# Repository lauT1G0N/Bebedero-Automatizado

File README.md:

el proyecto se trata de un bebedero automatizado para animales atreves de WI-FI
        tiene la capacidad de medir el nivel del agua y autoabastecer la misma ,

ES UN PROYECTO ENFOCADO EN LA PREVENCION DEL DESPERDICIO DE AGUA Y EN LA AUTOMATIZACION PARA AGILIZAR EL TIMEPO

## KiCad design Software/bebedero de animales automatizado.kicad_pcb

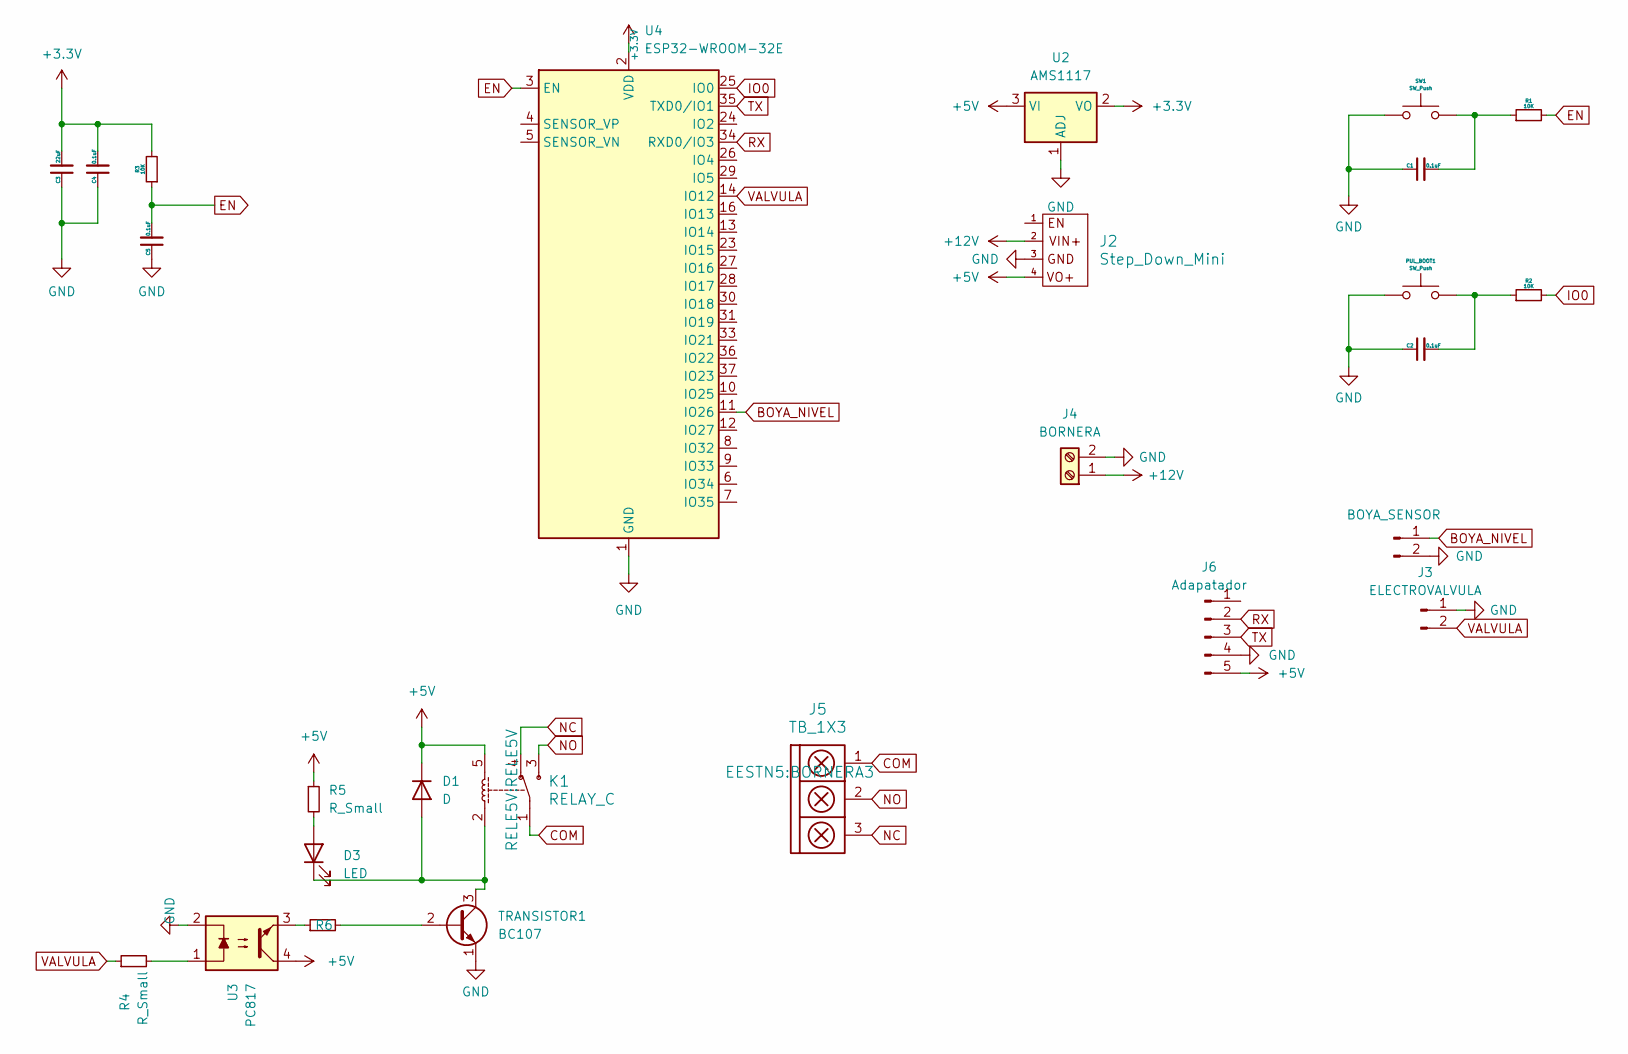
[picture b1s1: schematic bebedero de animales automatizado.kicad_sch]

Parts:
C1, C2, C4, C5: 0.1uF; C_0805
C3: 22uF; C_0805
D1: D; D_0805_2012Metric
D3: LED; LED_0805_2012Metric
J1: BOYA_SENSOR; PinHeader_1x02_P2.54mm_Vertical
J2: Step_Down_Mini; Mini360
J3: ELECTROVALVULA; PinHeader_1x02_P2.54mm_Vertical
J4: BORNERA; BORNERA2_AZUL
J5: TB_1X3; BORNERA3
J6: Adapatador; PinHeader_1x05_P2.54mm_Vertical
K1: RELAY_C; RELE5V
PUL_BOOT1: SW_Push; SW_PUSH_6mm_H5mm
R1, R2, R3: 10K; R_0805_2012Metric
R4, R5, R6: R_Small; R_0805_2012Metric
SW1: SW_Push; SW_PUSH_6mm_H5mm
TRANSISTOR1: BC107; TO-18-3
U2: AMS1117; SOT223-TAB2
U3: PC817; SOIC254P960X420-4N
U4: ESP32-WROOM-32E; ESP32-WROOM-32D

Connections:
+3.3V: C3.2, C4.2, R3.2, U2.2 (VO), U4.2 (VDD)
+5V: D1.1 (K), J2.4, J6.5, K1.5, R5.1, U2.3 (VI), U3.4
+12V: J2.2, J4.1
BOYA_NIVEL: J1.1, U4.11 (IO26)
COM: J5.1, K1.1
EN: C5.2, R1.2, R3.1, U4.3 (EN)
GND: C1.1, C2.1, C3.1, C4.1, C5.1, J1.2, J2.3, J3.1, J4.2, J6.4, PUL_BOOT1.1, SW1.1, TRANSISTOR1.1 (E), U2.1 (ADJ), U3.2, U4.1 (GND), U4.15 (GND), U4.38 (GND), U4.39 (GND)
IO0: R2.2, U4.25 (IO0)
NC: J5.3, K1.4
NO: J5.2, K1.3
unnamed: C1.2, R1.1, SW1.2
unnamed: C2.2, PUL_BOOT1.2, R2.1
unnamed: D1.2 (A), D3.1 (K), K1.2, TRANSISTOR1.3 (C)
unnamed: D3.2 (A), R5.2
unnamed: R4.2, U3.1
unnamed: R6.1, U3.3
unnamed: R6.2, TRANSISTOR1.2 (B)
RX: J6.2, U4.34 (RXD0/IO3)
TX: J6.3, U4.35 (TXD0/IO1)
VALVULA: J3.2, R4.1, U4.14 (IO12)

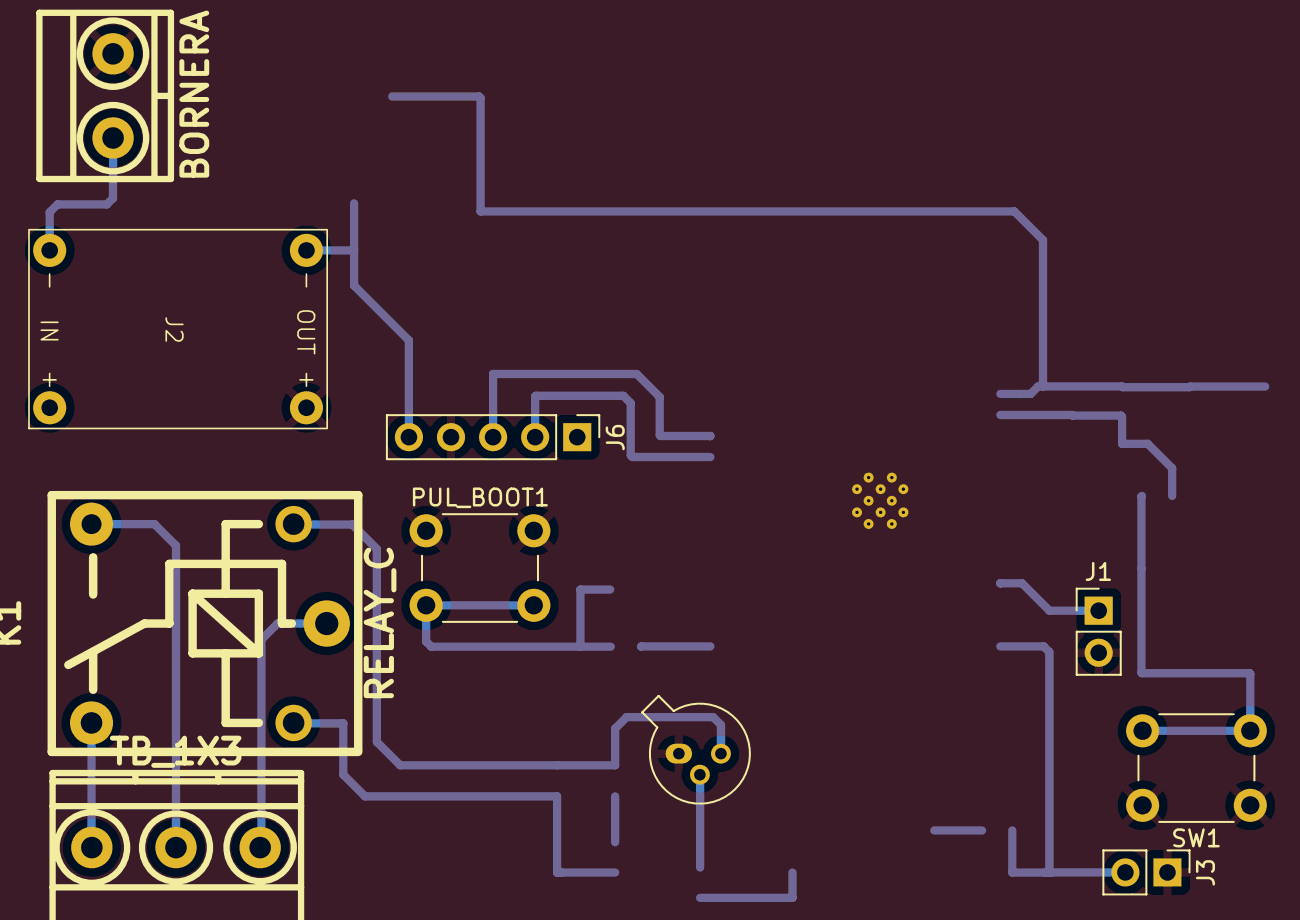
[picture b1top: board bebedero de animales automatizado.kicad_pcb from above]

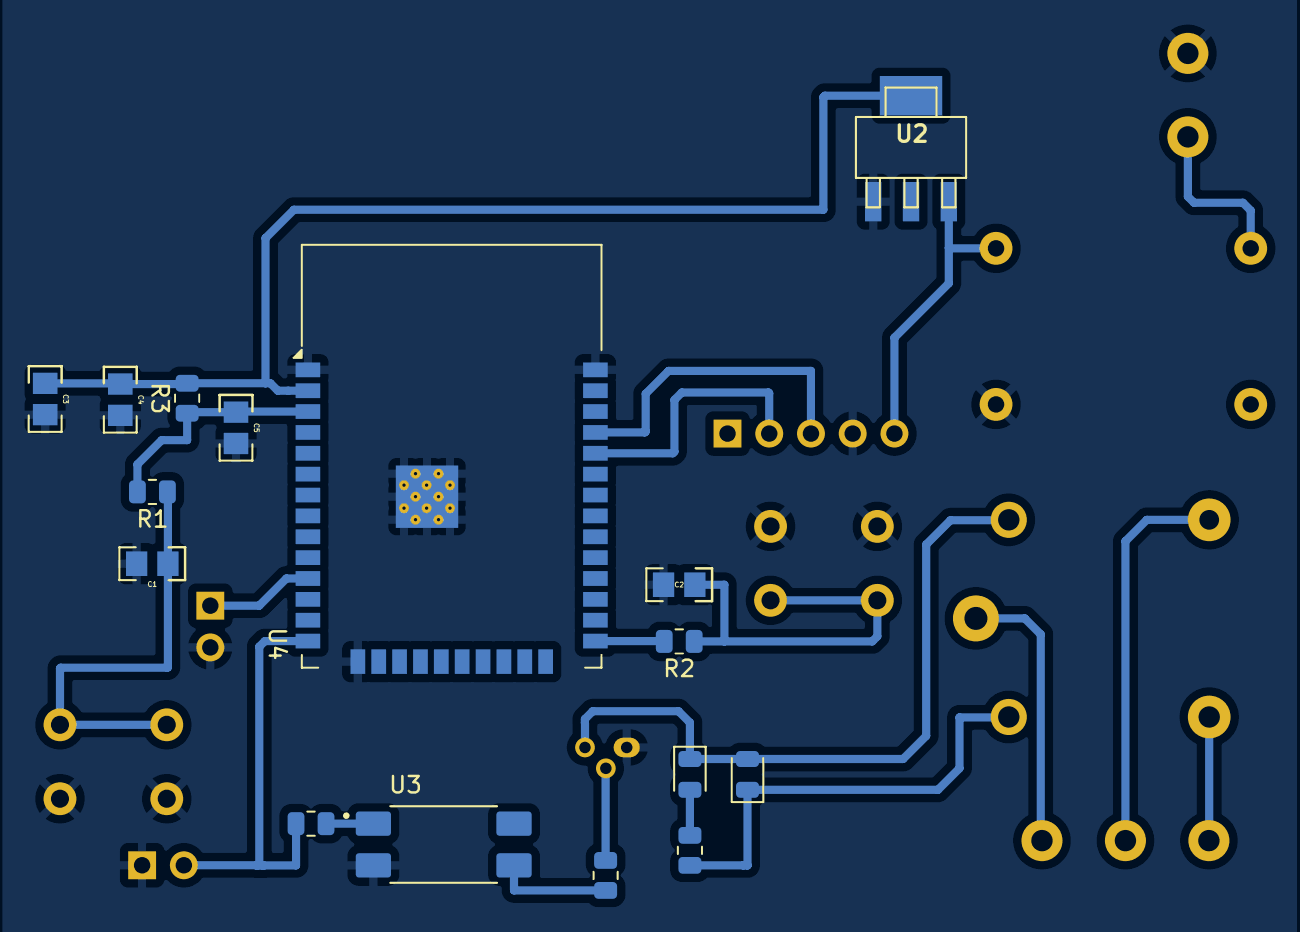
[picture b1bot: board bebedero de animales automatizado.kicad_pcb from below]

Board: 2 copper layers, 26 parts (16 on the bottom side), 20 nets.

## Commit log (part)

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2019-12-07 se crearon las carpetas
